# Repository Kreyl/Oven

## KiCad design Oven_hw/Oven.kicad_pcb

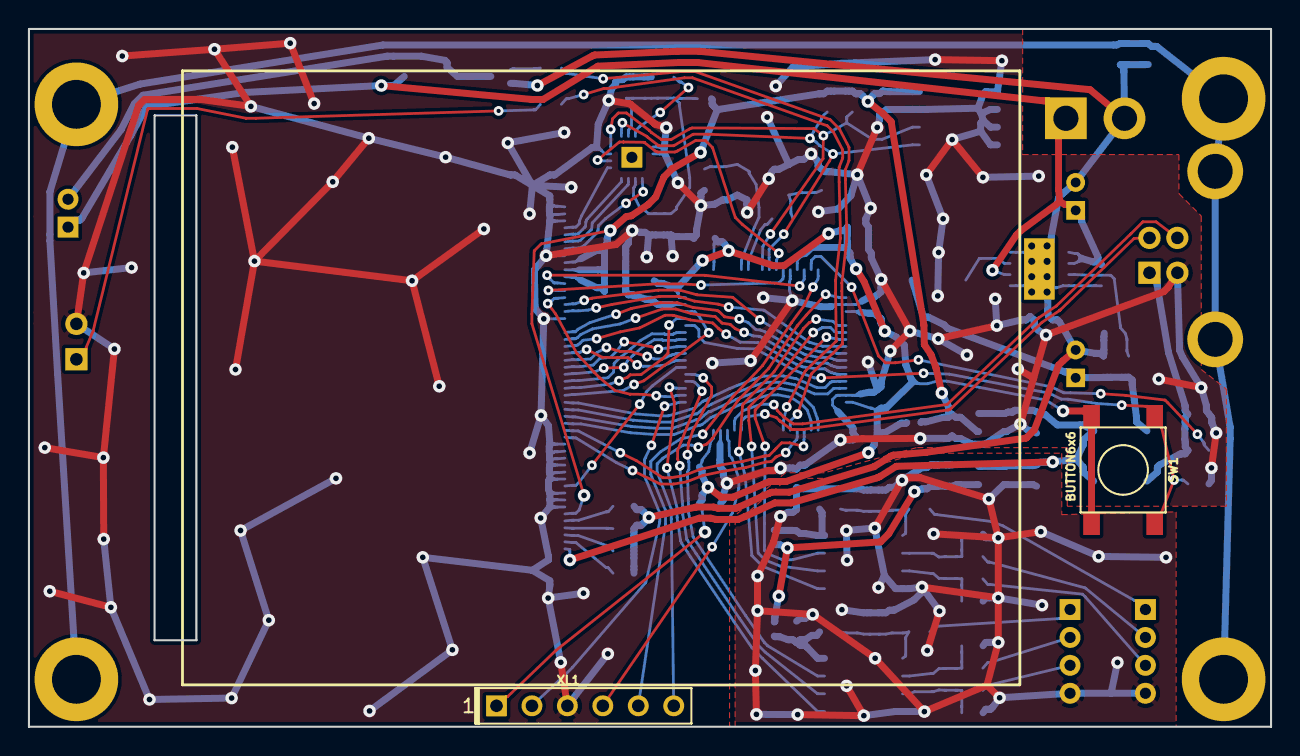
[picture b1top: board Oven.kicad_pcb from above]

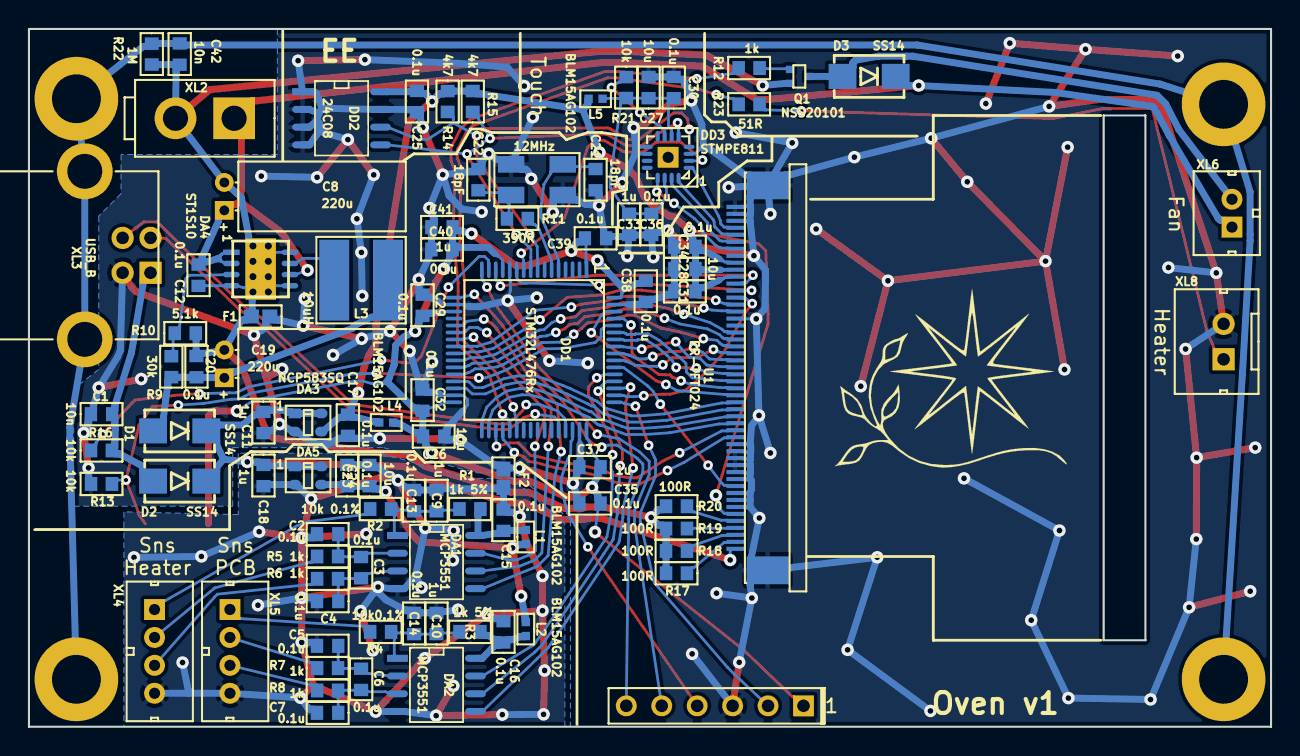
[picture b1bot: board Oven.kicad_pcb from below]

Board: 2 copper layers, 89.0 x 50.0 mm, 99 parts (93 on the bottom side), 84 nets.

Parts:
C1, C42: 10n; CAP_0603
C2, C3, C4, C5, C6, C7, C12, C13, C14, C15, C16, C17, C20, C23, C25, C29, C30, C31, C32, C34, C35, C36, C38, C39, C40: 0.1u; CAP_0603
C8, C19: 220u; CAP_05xxR_horiz
C9, C10, C11, C18, C33, C37, C41: 1u; CAP_0603
C21, C22: 18pF; CAP_0603
C24, C26, C27, C28: 10u; CAP_0603
D1, D2, D3: SS14; SMA_DO214AC
DA1, DA2: MCP3551; SO8_150MIL
DA3, DA5: NCP583SQ; SC82AB
DA4: ST1S10; DFN8
DD1: STM32L476Rx; LQFP64
DD2: 24C08; SO8_150MIL
DD3: STMPE811; QFN16_4x4_H
F1, F2: Fuse0R; RES_0603_FUSE
HOLE1, HOLE2, HOLE3, HOLE4: HOLE_METALLED; Hole3_5_out6mm
L1, L2, L4, L5: BLM15AG102; IND_0402
L3: 10uH; IND_SDR0604
Logo1: Logo; Ostranna_16d9_13d5
Q1: NSS20101; SC89-3
R1, R3: 1k 5%; RES_0603
R2: 10k 0.1%; RES_0603
R4: 10k0.1%; RES_0603
R5, R6, R7, R8, R12: 1k; RES_0603
R9: 30k; RES_0603
R10: 5.1k; RES_0603
R11: 390R; RES_0603
R13, R16, R21: 10k; RES_0603
R14, R15: 4k7; RES_0603
R17, R18, R19, R20: 100R; RES_0603
R22: 1M; RES_0603
R23: 51R; RES_0603
SW1: BUTTON6x6; BTN_6x6
U1: ER-TFT024; ER-CON50HT-1
XL1: CONN_6; PLS-6
XL2: CONN_2; MINIFIT2x1_S_VERT
XL3: USB_B
XL4, XL5: CONN_4; WB-04(MW-4M)
XL6: CONN_2; WB-02(MW-2M)
XL8: CONN_2; W02_Pitch_2d54
XTAL1: 12MHz; 0503x4-4

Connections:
+3.3V: C17.1, C25.2, C28.1, C31.1, C34.1, DA3.3, DD2.8, L4.2, L5.2, R14.1, R15.2, U1.6, U1.40, U1.41, U1.42
+3.3V_A: C23.1, C24.1, DA5.3, L1.1, L2.1
+5V: C11.1, C18.1, D1.C, D2.C, DA3.1, DA3.4, DA5.1, DA5.4, U1.1
+12V: C8.1, C12.1, D3.C, DA4.1, DA4.2, DA4.6, XL2.1, XL6.1
/5V_USB: C1.2, D2.A, R16.2, XL3.1
/ADC_PWR1: C15.1, DA1.8, L1.2, R1.1
/ADC_PWR2: C16.1, DA2.8, L2.2, R3.1
/CS1: DA1.7, DD1.23
/CS2: DA2.7, DD1.53
/D+: DD1.45, XL3.3
/D-: DD1.44, XL3.2
/HEATER_CTRL: DD1.38, R23.1
/LCD_CSX: DD1.11, U1.38
/LCD_D0: DD1.26, U1.32
/LCD_D1: DD1.27, U1.31
/LCD_D2: DD1.28, U1.30
/LCD_D3: DD1.55, U1.29
/LCD_D4: DD1.56, U1.28
/LCD_D5: DD1.57, U1.27
/LCD_D6: DD1.58, U1.26
/LCD_D7: DD1.59, U1.25
/LCD_D8: DD1.61, U1.24
/LCD_D9: DD1.62, U1.23
/LCD_D10: DD1.29, U1.22
/LCD_D11: DD1.30, U1.21
/LCD_D12: DD1.33, U1.20
/LCD_D13: DD1.34, U1.19
/LCD_D14: DD1.35, U1.18
/LCD_D15: DD1.36, U1.17
/LCD_DC: DD1.50, U1.37
/LCD_RD: DD1.24, U1.35
/LCD_RST: DD1.54, U1.10
/LCD_TE: DD1.14, U1.39
/LCD_WR: DD1.25, U1.36
/LCD_X+: DD3.13, U1.44
/LCD_X-: DD3.16, U1.46
/LCD_Y+: DD3.15, U1.45
/LCD_Y-: DD3.1, U1.47
/L_OUT: DA4.7, L3.2
/PWR_5V: C19.1, C20.1, D1.A, L3.1, R9.1
/SCK1: DA1.5, DD1.21
/SCK2: DA2.5, DD1.51
/SCL: DD1.8, DD2.6, DD3.4, R14.2
/SDA: DD1.9, DD2.5, DD3.5, R15.1
/SDO1: DA1.6, DD1.22
/SDO2: DA2.6, DD1.52
/SHLD: C42.2, HOLE1.H, HOLE2.H, HOLE3.H, HOLE4.H, R22.1, XL3.H
/SWCLK: DD1.49, XL1.2
/SWDIO: DD1.46, XL1.4
/TOUCH_INT: DD1.10, DD3.2
/TOUCH_PWR: C27.1, C30.1, C33.1, C36.1, DD3.6, DD3.14, L5.1, R21.2
/UART_RX: DD1.17, XL1.6
/UART_TX: DD1.16, XL1.5
/VENT_CTRL: DD1.37, R12.1
/VENT_OUT: D3.A, Q1.3, XL6.2
AGND: C2.1, C4.2, C5.1, C7.2, C9.2, C10.2, C13.2, C14.2, C15.2, C16.2, C18.2, C23.2, C24.2, DA1.4, DA2.4, DA5.2, F2.1, XL4.4, XL5.4
GND: C1.1, C11.2, C17.2, C21.2, C22.2, C25.1, C26.1, C27.2, C28.2, C29.1, C30.2, C31.2, C32.1, C33.2, C34.2, C35.1, C36.2, C37.1, C38.1, C39.1, C40.1, C41.1, DA3.2, DD1.12, DD1.18, DD1.31, DD1.47, DD1.63, DD2.1, DD2.2, DD2.3, DD2.4, DD2.7, DD3.3, DD3.9, DD3.10, F1.1, F2.2, R13.2, U1.7, U1.8, U1.9, U1.11, U1.12, U1.13, U1.14, U1.15, U1.16, U1.34, U1.43, U1.48, U1.49, U1.50, U1.H, XL1.3, XL3.4, XL8.2, XTAL1.H
GNDPWR: C8.2, C12.2, C19.2, C20.2, C42.1, DA4.4, DA4.5, DA4.8, DA4.PAD, F1.2, Q1.2, R10.2, R17.2, R18.2, R19.2, R20.2, R22.2, XL2.2
unnamed: C2.2, C3.1, DA1.2, R5.2
unnamed: C3.2, C4.1, DA1.3, R6.2
unnamed: C5.2, C6.1, DA2.2, R7.2
unnamed: C6.2, C7.1, DA2.3, R8.2
unnamed: C10.1, C14.1, DA2.1, R3.2, R4.1
unnamed: C9.1, C13.1, DA1.1, R1.2, R2.1
unnamed: C21.1, DD1.5, XTAL1.1
unnamed: C22.1, R11.1, XTAL1.2
unnamed: DA4.3, R9.2, R10.1
unnamed: DD1.6, R11.2
unnamed: DD1.15, R16.1
unnamed: DD1.60, R13.1, SW1.1
unnamed: DD3.7, R21.1
unnamed: Q1.1, R12.2
unnamed: R2.2, XL4.1
unnamed: R4.2, XL5.1
unnamed: R5.1, XL4.2
unnamed: R6.1, XL4.3
unnamed: R7.1, XL5.2
unnamed: R8.1, XL5.3
unnamed: R17.1, U1.2
unnamed: R18.1, U1.3
unnamed: R19.1, U1.4
unnamed: R20.1, U1.5
unnamed: R23.2, XL8.1
PwrMCU: C26.2, C29.2, C32.2, C35.2, C37.2, C38.2, C39.2, C40.2, C41.2, DD1.1, DD1.13, DD1.19, DD1.32, DD1.48, DD1.64, L4.1, SW1.2, XL1.1

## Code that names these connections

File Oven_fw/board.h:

/*
 * board.h
 *
 *  Created on: 12 ñåíò. 2015 ã.
 *      Author: Kreyl
 */

#pragma once

#include <inttypes.h>

// ==== General ====
#define BOARD_NAME          "Oven"
// MCU type as defined in the ST header.
#define STM32L476xx

// Freq of external crystal if any. Leave it here even if not used.
#define CRYSTAL_FREQ_HZ         12000000

// OS timer settings
#define STM32_ST_IRQ_PRIORITY   2
#define STM32_ST_USE_TIMER      5
#define SYS_TIM_CLK             (Clk.APB1FreqHz)    // Timer 5 is clocked by APB1

//  Periphery
#define I2C1_ENABLED            FALSE
#define I2C2_ENABLED            FALSE
#define I2C3_ENABLED            TRUE

#define ADC_REQUIRED            FALSE
#define STM32_DMA_REQUIRED      TRUE    // Leave this macro name for OS

// LCD
#define LCD_W           320 // }
#define LCD_H           240 // } Pixels count

#if 1 // ========================== GPIO =======================================
// UART
#define UART_GPIO       GPIOA
#define UART_TX_PIN     2
#define UART_RX_PIN     3
#define UART_AF         AF7 // for all USARTs

// LCD
#define LCD_DATA_GPIO   GPIOB
#define LCD_RESET_GPIO  GPIOD
#define LCD_RESET_PIN   2
#define LCD_CSX_GPIO    GPIOC
#define LCD_CSX_PIN     3
#define LCD_DC_GPIO     GPIOA
#define LCD_DC_PIN      15
#define LCD_WR_GPIO     GPIOC
#define LCD_WR_PIN      5
#define LCD_RD_GPIO     GPIOC
#define LCD_RD_PIN      4
#define LCD_TE_GPIO     GPIOA
#define LCD_TE_PIN      0

// Touch
#define TOUCH_INT_GPIO  GPIOC
#define TOUCH_INT_PIN   2

// I2C
#define I2C1_GPIO       GPIOB
#define I2C1_SCL        6
#define I2C1_SDA        7
#define I2C2_GPIO       GPIOB
#define I2C2_SCL        10
#define I2C2_SDA        11
#define I2C3_GPIO       GPIOC
#define I2C3_SCL        0
#define I2C3_SDA        1

#define I2C3_AF         AF4

// ADCs: GPIO, CS, CLK, SDO, Alterfunc, Spi
#define ADC_H_SETUP     { GPIOA,  7,  5, 6,  AF5, SPI1 }
#define ADC_P_SETUP     { GPIOC, 12, 10, 11, AF6, SPI3 }

// Outputs
#define HEATER_TOP      10000
#define HEATER_SETUP    { GPIOC, 7, TIM8, 2, invNotInverted, omPushPull, HEATER_TOP }
#define FAN_SETUP       { GPIOC, 6, TIM3, 1, invNotInverted, omPushPull, 100 }

#endif // GPIO

#if 1 // ========================= Timer =======================================
//#define TMR_DAC_CHUNK               TIM6
//#define TMR_DAC_SMPL                TIM7
//#define TMR_DAC_CHUNK_IRQ           TIM6_IRQn
//#define TMR_DAC_CHUNK_IRQ_HANDLER   VectorEC
#endif // Timer

#if 1 // =========================== SPI =======================================
#define ADC_H_SPI       SPI1
#define ADC_P_SPI       SPI3
#endif

#if 1 // =========================== I2C =======================================
#define I2C_TOUCH       i2c3
#endif

#if 1 // ========================== USART ======================================
#define UART            USART2
#define UART_TX_REG     UART->TDR
#define UART_RX_REG     UART->RDR
#define PRINTF_FLOAT_EN TRUE
#endif

#if ADC_REQUIRED // ======================= Inner ADC ==========================
// Clock divider: clock is generated from the APB2
#define ADC_CLK_DIVIDER		adcDiv2

// ADC channels
#define BAT_CHNL 	        1

#define ADC_VREFINT_CHNL    17  // All 4xx and F072 devices. Do not change.
#define ADC_CHANNELS        { BAT_CHNL, ADC_VREFINT_CHNL }
#define ADC_CHANNEL_CNT     2   // Do not use countof(AdcChannels) as preprocessor does not know what is countof => cannot check
#define ADC_SAMPLE_TIME     ast55d5Cycles
#define ADC_SAMPLE_CNT      8   // How many times to measure every channel

#define ADC_MAX_SEQ_LEN     16  // 1...16; Const, see ref man
#define ADC_SEQ_LEN         (ADC_SAMPLE_CNT * ADC_CHANNEL_CNT)
#if (ADC_SEQ_LEN > ADC_MAX_SEQ_LEN) || (ADC_SEQ_LEN == 0)
#error "Wrong ADC channel count and sample count"
#endif
#endif

#if 1 // =========================== DMA =======================================
// ==== Uart ====
// Remap is made automatically if required
#define UART_DMA_TX     STM32_DMA1_STREAM7
#define UART_DMA_RX     STM32_DMA1_STREAM6
#define UART_DMA_CHNL   2

// DAC
//#define DAC_DMA         STM32_DMA1_STREAM2

// ==== I2C ====
#define I2C1_DMA_TX     STM32_DMA2_STREAM7
#define I2C1_DMA_RX     STM32_DMA1_STREAM6
#define I2C1_DMA_CHNL   5
#define I2C2_DMA_TX     STM32_DMA1_STREAM4
#define I2C2_DMA_RX     STM32_DMA1_STREAM5
#define I2C2_DMA_CHNL   3
#define I2C3_DMA_TX     STM32_DMA1_STREAM2
#define I2C3_DMA_RX     STM32_DMA1_STREAM3
#define I2C3_DMA_CHNL   3

#define STM32_I2C_I2C3_RX_DMA_STREAM   STM32_DMA_STREAM_ID(1, 3)
#define STM32_I2C_I2C3_TX_DMA_STREAM   STM32_DMA_STREAM_ID(1, 2)


#if ADC_REQUIRED
/* DMA request mapped on this DMA channel only if the corresponding remapping bit is cleared in the SYSCFG_CFGR1
 * register. For more details, please refer to Section10.1.1: SYSCFG configuration register 1 (SYSCFG_CFGR1) on
 * page173 */
#define ADC_DMA         STM32_DMA1_STREAM1
#define ADC_DMA_MODE    STM32_DMA_CR_CHSEL(0) |   /* DMA2 Stream4 Channel0 */ \
                        DMA_PRIORITY_LOW | \
                        STM32_DMA_CR_MSIZE_HWORD | \
                        STM32_DMA_CR_PSIZE_HWORD | \
                        STM32_DMA_CR_MINC |       /* Memory pointer increase */ \
                        STM32_DMA_CR_DIR_P2M |    /* Direction is peripheral to memory */ \
                        STM32_DMA_CR_TCIE         /* Enable Transmission Complete IRQ */
#endif // ADC

#endif // DMA

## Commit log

2016-04-18 + Old oven
2016-04-18 - Old oven
2016-04-26 + Sch started
2016-04-27 + sch started (with er-tft024 screen)
2016-04-27 + Sch with nokia LCD
2016-04-27 + Resistive display is back
2016-04-29 Short PCB
2016-04-29 + PCB sent to factory
2016-05-12 + FW Uart works
2016-05-13 Started with ugfx
2016-05-13 + first CLS of LCD
2016-05-13 * Some clean-up
2016-05-13 + try of self-made gui
2016-05-13 + Color blended buttons
2016-05-14 Fighting with fonts - no big deal
2016-05-14 + Draw to buffer * ILI drv bug
2016-05-14 proceeding
2016-05-14 font templated
2016-05-14 + Alignment ok
2016-05-14 + Fonts + Button text's font
2016-05-14 cleanup
2016-05-14 + Touch reads coords
2016-05-15 + Page_t
2016-05-15 Switch to styles
2016-05-15 + Touch-Detouch received from display
2016-05-15 Btns pressed/depressed
2016-05-16 + ADC works But still waits too long
2016-05-16 + Both ADCs are operational
2016-05-16 + I2C protected by semaphore
2016-05-16 eeprom halfway
2016-06-16 Back to C-style pin manipulations due to speed impact
2016-06-16 Heater timer ok
2016-06-17 + float printf
2016-06-17 + integral part Dif part still based on err
2016-06-18 Good PID coefs
2016-06-23 Manual interface started
2016-06-23 Proceeding with interface
2016-06-23 + ADC filtering
2016-06-24 + t displayed
2016-06-24 Simple chart done
2016-06-24 Thermoprofile algorithm
2016-06-25 + Time displayed
2016-06-25 - Theme_t
2016-06-25 + t heater manual +-
2016-06-26 + chart vert line - chart spaghetti code
2016-06-27 + fnt tahoma Intermediate RC
